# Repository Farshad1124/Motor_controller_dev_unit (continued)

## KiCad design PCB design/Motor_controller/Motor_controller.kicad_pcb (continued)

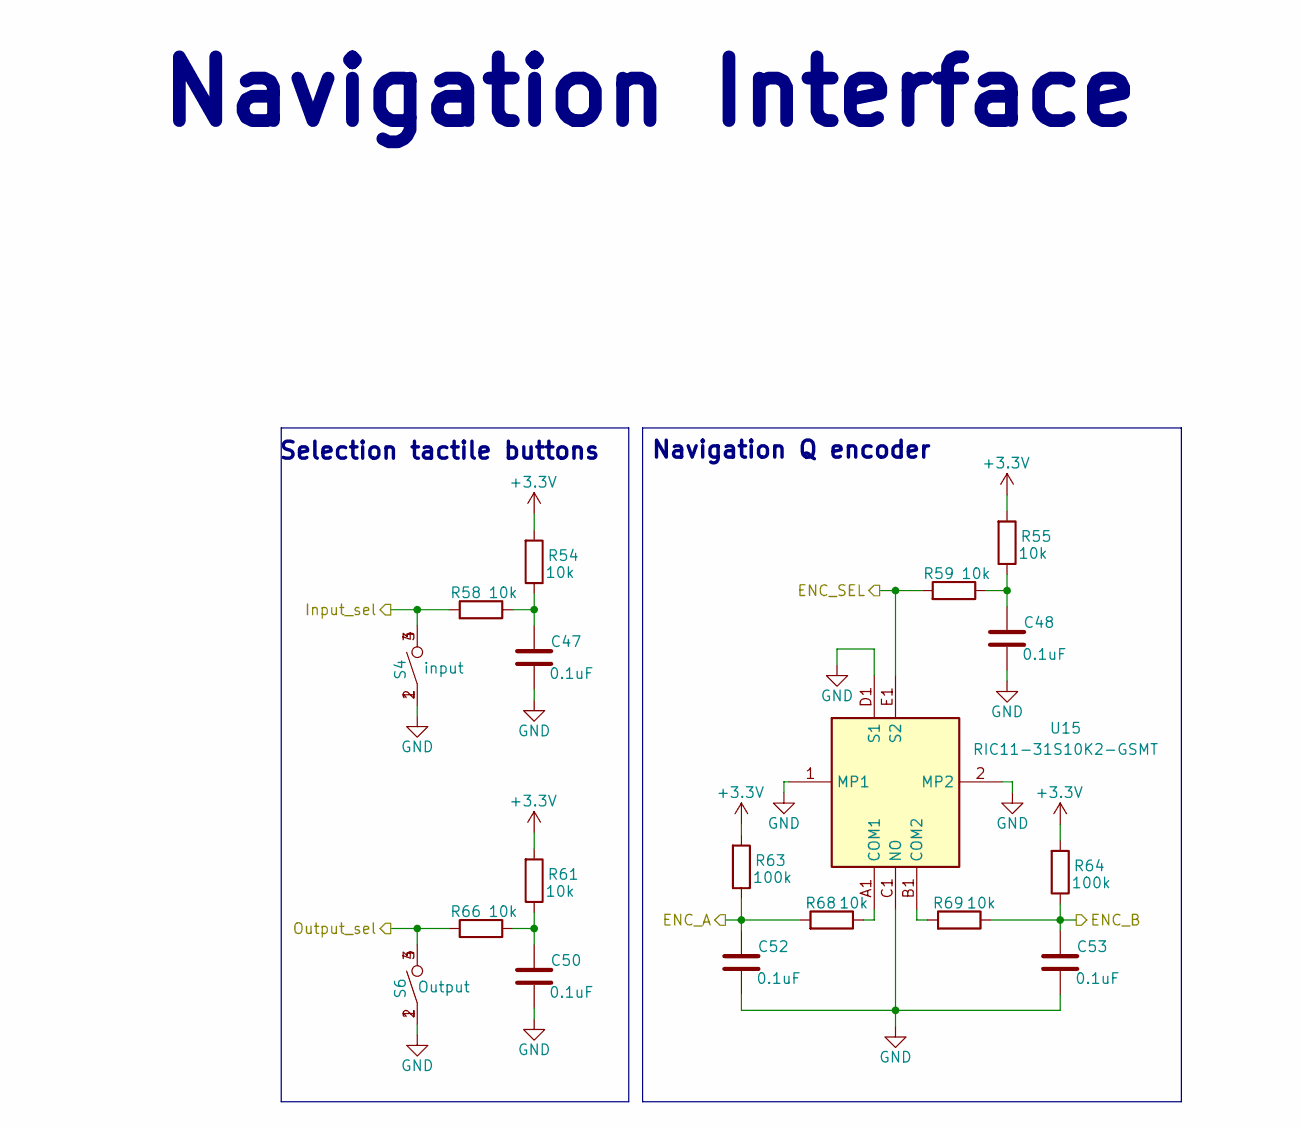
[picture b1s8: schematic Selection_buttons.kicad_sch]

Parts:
C47, C48, C50, C52, C53: 0.1uF; C_0603_1608Metric
R54, R55, R58, R59, R61, R66, R68, R69: 10k; R_0603_1608Metric
R63, R64: 100k; R_0603_1608Metric
S4: input; SMT_FS
S6: Output; SMT_FS
U15: RIC11-31S10K2-GSMT; RIC1131S10K2GSMT; Manufacturer_Part_Number RIC11-31S10K2-GSMT; Mouser Part Number 179-RIC1131S10K2GSMT

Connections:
+3.3V: R54.1, R55.1, R61.1, R63.1, R64.1; also elsewhere on the board
/ENC_A: C52.2, R63.2, R68.1; also elsewhere on the board
/ENC_B: C53.2, R64.2, R69.2; also elsewhere on the board
/ENC_SEL: R59.1, U15.E1 (S2); also elsewhere on the board
/Input_sel: R58.1, S4.3, S4.4; also elsewhere on the board
/Ouput_sel: R66.1, S6.3, S6.4; also elsewhere on the board
GND: C47.1, C48.1, C50.1, C52.1, C53.1, S4.1, S4.2, S6.1, S6.2, U15.1 (MP1), U15.2 (MP2), U15.C1 (NO), U15.D1 (S1); also elsewhere on the board
unnamed: C47.2, R54.2, R58.2
unnamed: C48.2, R55.2, R59.2
unnamed: C50.2, R61.2, R66.2
unnamed: R68.2, U15.A1 (COM1)
unnamed: R69.1, U15.B1 (COM2)

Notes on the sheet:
Navigation Interface
Selection tactile buttons
Navigation Q encoder

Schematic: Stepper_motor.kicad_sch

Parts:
C30, C31, C33: 0.1uF; C_0603_1608Metric
C32: 100uF; CAPAE660X600N; voltage 35v
J8: B4B-XH-A; JST_B4B-XH-A
J9: PHOENIX_1984633
J10: Conn_01x05_Pin; PinHeader_1x05_P2.54mm_Vertical
JP1, JP2, JP3: NPC02SXON-RC; TestPoint_2Pads_Pitch2.54mm_Drill0.8mm
R37: 10k; R_0603_1608Metric
R38, R39, R40: 100; R_0603_1608Metric
R41: 1k; R_0603_1608Metric
TP37, TP38, TP49, TP50, TP51: TestPoint; KEYSTONE_1031; PARTREV B
U11: NC7WZ14P6X; TSOT23-6_419BL_ONS
U12: TMC2208_SILENTSTEPSTICK; MODULE_TMC2208_SILENTSTEPSTICK

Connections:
+3.3V: C30.2, C31.2, C33.2, JP1.2 (B), JP2.2 (B), JP3.2 (B), R37.1, U11.5 (VCC), U12.JP2_7 (VIO); also elsewhere on the board
/SMDIR: R39.1; also elsewhere on the board
/SMEN: J10.5, R37.2, R38.2, U11.1 (A1), U12.JP1_8 (EN); also elsewhere on the board
/SMRX: J10.4, R41.1; also elsewhere on the board
/SMSTEP: R40.1; also elsewhere on the board
/SMTX: J10.3, JP1.1 (A), R41.2, U12.JP1_5 (PDN/UART2); also elsewhere on the board
/Stepper motor/DR: J10.1, R39.2, U12.JP1_1 (DIR)
/Stepper motor/OA1: J8.2, J9.2, TP49.TP, U12.JP2_4 (OA1)
/Stepper motor/OA2: J8.3, J9.3, TP50.TP, U12.JP2_3 (OA2)
/Stepper motor/OB1: J8.1, J9.1, TP38.TP, U12.JP2_5 (OB1)
/Stepper motor/OB2: J8.4, J9.4, TP51.TP, U12.JP2_6 (OB2)
/Stepper motor/STP: J10.2, R40.2, U12.JP1_2 (STEP)
GND: C30.1, C31.1, C32.2, C33.1, TP37.TP, U11.2 (GND), U12.JP2_2 (GND), U12.JP2_8 (GND); also elsewhere on the board
unnamed: JP2.1 (A), U12.JP1_7 (MS1)
unnamed: JP3.1 (A), U12.JP1_6 (MS2)
unnamed: R38.1, U11.6 (Y1)
unnamed: U12.JP1_3 (CLK), U12.JP1_4 (PDN/UART1)
VSM: C32.1, U12.JP2_1 (VM); also elsewhere on the board

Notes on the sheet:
Stepper Motor Driver

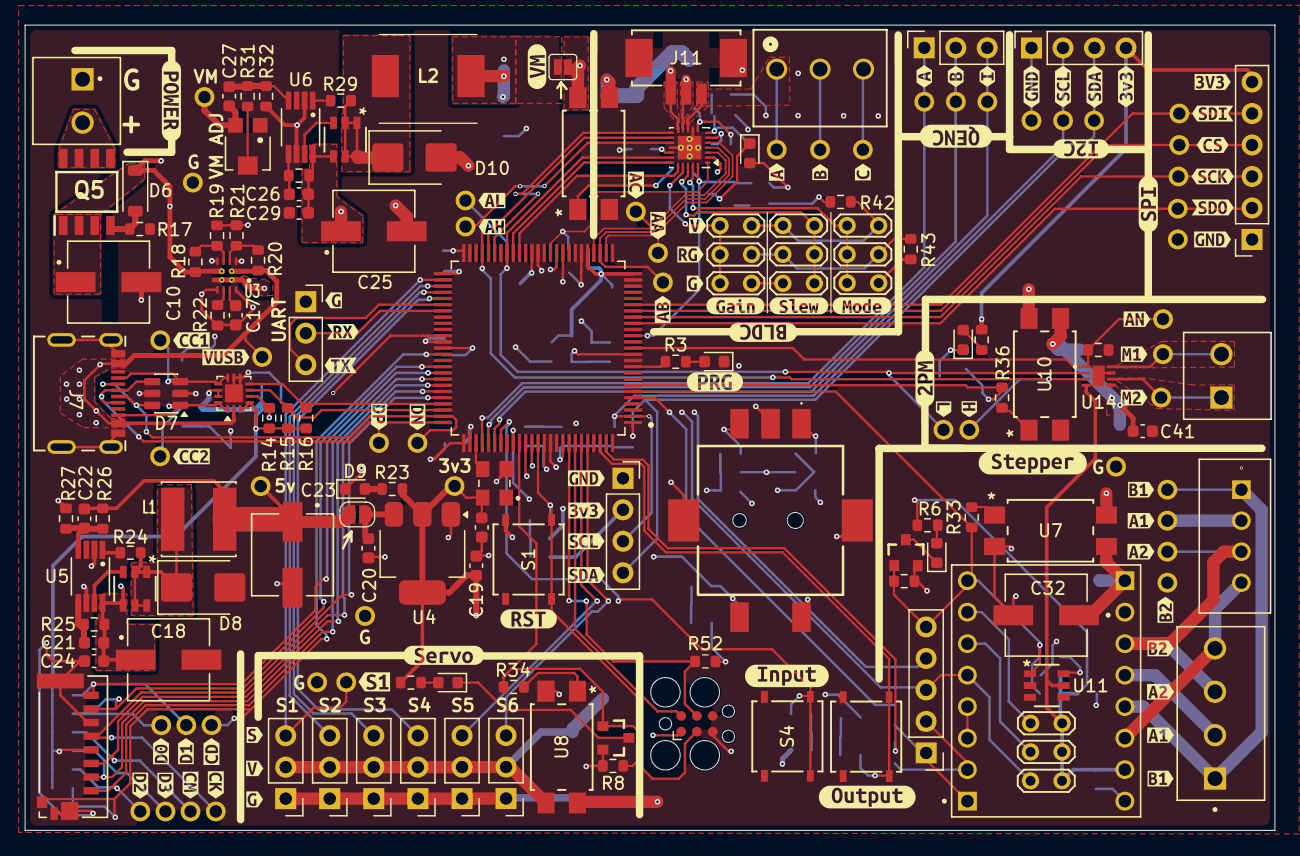
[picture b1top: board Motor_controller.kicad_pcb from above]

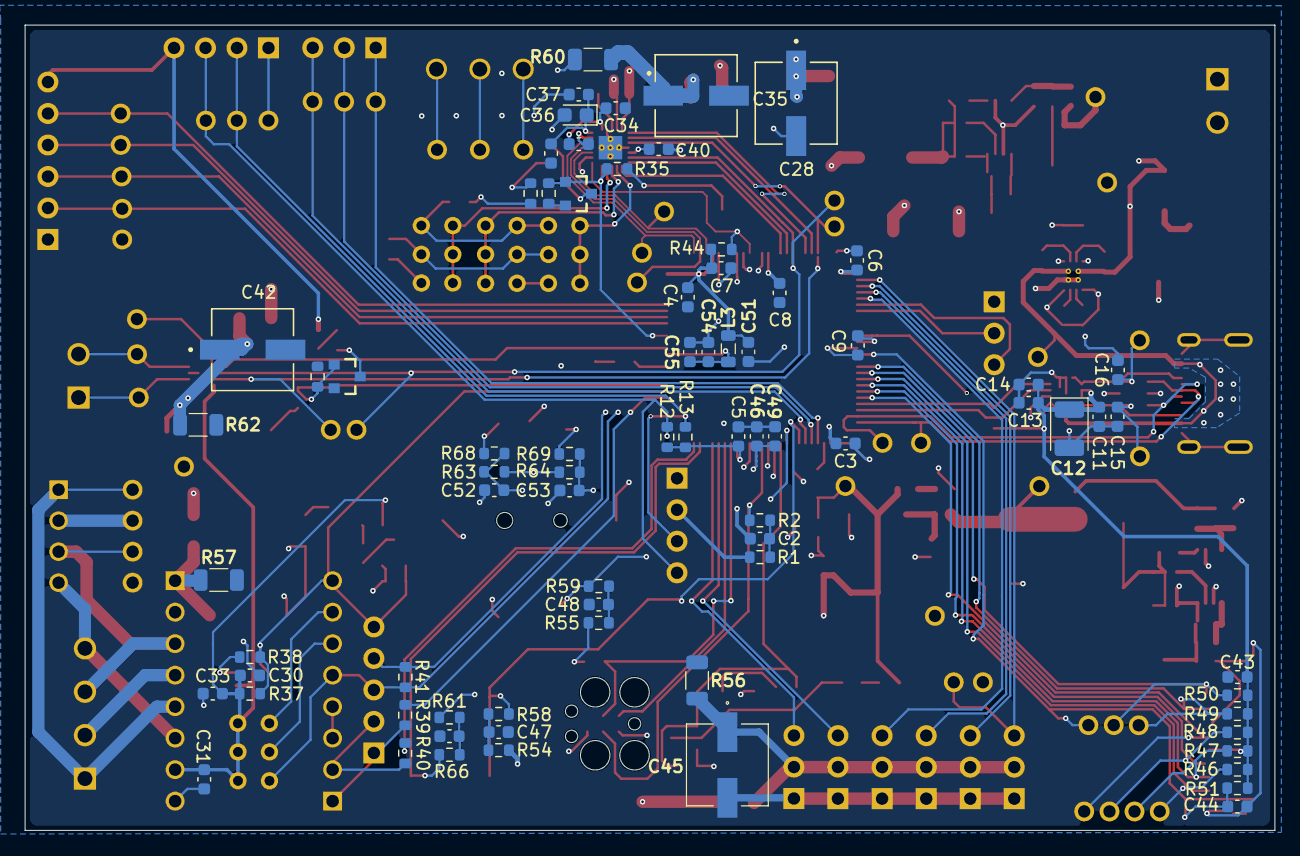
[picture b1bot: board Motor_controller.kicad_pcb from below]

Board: 4 copper layers, 100.8 x 65.0 mm, 319 parts (76 on the bottom side), 134 nets.

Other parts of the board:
kibuzzard-6A6A84AC: G***; kibuzzard-6A6A84AC
kibuzzard-6A6A843B: G***; kibuzzard-6A6A843B
kibuzzard-6A6A844C: G***; kibuzzard-6A6A844C
kibuzzard-6A6A845F: G***; kibuzzard-6A6A845F
kibuzzard-6A6A846C: G***; kibuzzard-6A6A846C
kibuzzard-6A6A8483: G***; kibuzzard-6A6A8483
kibuzzard-6A6A8495: G***; kibuzzard-6A6A8495
kibuzzard-6A6AA16F: G***; kibuzzard-6A6AA16F
kibuzzard-6A6AB0B9: G***; kibuzzard-6A6AB0B9
kibuzzard-6A6AB018: G***; kibuzzard-6A6AB018
kibuzzard-6A6AB028: G***; kibuzzard-6A6AB028
kibuzzard-6A6AB55B: G***; kibuzzard-6A6AB55B
kibuzzard-6A6AB65C: G***; kibuzzard-6A6AB65C
kibuzzard-6A6AB333: G***; kibuzzard-6A6AB333
kibuzzard-6A6AB573: G***; kibuzzard-6A6AB573
kibuzzard-6A6AB741: G***; kibuzzard-6A6AB741
kibuzzard-6A6AB750: G***; kibuzzard-6A6AB750
kibuzzard-6A6D000A: G***; kibuzzard-6A6D000A
kibuzzard-6A6D3F7B: G***; kibuzzard-6A6D3F7B
kibuzzard-6A9B0FE9: G***; kibuzzard-6A9B0FE9
kibuzzard-6A9B0FFC: G***; kibuzzard-6A9B0FFC
kibuzzard-6A67A6FB: G***; kibuzzard-6A67A6FB
kibuzzard-6A67A717: G***; kibuzzard-6A67A717
kibuzzard-6A67B8BD: G***; kibuzzard-6A67B8BD
kibuzzard-6A67B82C: G***; kibuzzard-6A67B82C
kibuzzard-6A67B858: G***; kibuzzard-6A67B858
kibuzzard-6A67D5B7: G***; kibuzzard-6A67D5B7
kibuzzard-6A67D5C9: G***; kibuzzard-6A67D5C9
kibuzzard-6A67D598: G***; kibuzzard-6A67D598
kibuzzard-6A67D603: G***; kibuzzard-6A67D603
kibuzzard-6A67D617: G***; kibuzzard-6A67D617
kibuzzard-6A67D637: G***; kibuzzard-6A67D637
kibuzzard-6A67E5CB: G***; kibuzzard-6A67E5CB
kibuzzard-6A67E545: G***; kibuzzard-6A67E545
kibuzzard-6A67E571: G***; kibuzzard-6A67E571
kibuzzard-6A67F9C7: G***; kibuzzard-6A67F9C7
kibuzzard-6A67F9D9: G***; kibuzzard-6A67F9D9
kibuzzard-6A67F044: G***; kibuzzard-6A67F044
kibuzzard-6A67F87C: G***; kibuzzard-6A67F87C
kibuzzard-6A67F891: G***; kibuzzard-6A67F891
kibuzzard-6A67FEEF: G***; kibuzzard-6A67FEEF
kibuzzard-6A67FFFA: G***; kibuzzard-6A67FFFA
kibuzzard-6A679C3C: G***; kibuzzard-6A679C3C
kibuzzard-6A679C8A: G***; kibuzzard-6A679C8A
kibuzzard-6A679C30: G***; kibuzzard-6A679C30
kibuzzard-6A679C76: G***; kibuzzard-6A679C76
kibuzzard-6A679C91: G***; kibuzzard-6A679C91
kibuzzard-6A679C97: G***; kibuzzard-6A679C97
kibuzzard-6A680EB7: G***; kibuzzard-6A680EB7
kibuzzard-6A680F4D: G***; kibuzzard-6A680F4D
kibuzzard-6A680F98: G***; kibuzzard-6A680F98
kibuzzard-6A680FB2: G***; kibuzzard-6A680FB2
kibuzzard-6A680FF5: G***; kibuzzard-6A680FF5
kibuzzard-6A6800E6: G***; kibuzzard-6A6800E6
kibuzzard-6A6800F9: G***; kibuzzard-6A6800F9
kibuzzard-6A6815D2: G***; kibuzzard-6A6815D2
kibuzzard-6A6822BB: G***; kibuzzard-6A6822BB
kibuzzard-6A6822D3: G***; kibuzzard-6A6822D3
kibuzzard-6A6829BB: G***; kibuzzard-6A6829BB
kibuzzard-6A6977BF: G***; kibuzzard-6A6977BF
kibuzzard-6A69714E, kibuzzard-6A69714E#2: G***; kibuzzard-6A69714E
kibuzzard-6A680004: G***; kibuzzard-6A680004
kibuzzard-6A680011: G***; kibuzzard-6A680011
kibuzzard-6A680102: G***; kibuzzard-6A680102
kibuzzard-6A680116: G***; kibuzzard-6A680116
kibuzzard-6A680514: G***; kibuzzard-6A680514
kibuzzard-6A680958: G***; kibuzzard-6A680958
kibuzzard-6A680974: G***; kibuzzard-6A680974
kibuzzard-6A681364: G***; kibuzzard-6A681364
kibuzzard-6A697161, kibuzzard-6A697161#2: G***; kibuzzard-6A697161
kibuzzard-6A697186, kibuzzard-6A697186#2: G***; kibuzzard-6A697186
kibuzzard-6A697195, kibuzzard-6A697195#2: G***; kibuzzard-6A697195

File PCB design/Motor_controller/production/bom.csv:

Designator,Footprint,Quantity,Value,LCSC Part #
"C1, C11, C14, C2, C24, C29, C3, C30, C31, C33, C34, C37, C4, C41, C43, C44, C47, C48, C49, C5, C50, C52, C53, C55, C6, C7, C8, C9",0603,28,0.1uF,
"C10, C18, C25",CAPAE660X600N,3,22uF,
C12,CP_EIA-3528-12_Kemet-T,1,100uF,
"C13, C17",0603,2,1uF,
"C15, C16",0603,2,330pF,
"C19, C51, C54",0603,3,10uF,
"C20, C38, C39",0603,3,100nF,
"C21, C26",0603,2,1nF,
"C22, C27",0603,2,100pF,
"C23, C28, C32, C45",CAPAE660X600N,4,100uF,
"C35, C42",CAPAE660X600N,2,10uF,
C36,CP_EIA-2012-12_Kemet-R,1,10uF,
"C40, C46",0603,2,4.7uf,
"D1, D2, D3, D4, D5, D9",0603,6,LED,
"D10, D8",D_SMB,2,10BQ040,
D6,D_SOD-123,1,BZT52B12,
D7,SOT-23-6,1,ESDA6V1BC6,
J10,PinHeader_1x05_P2.54mm_Vertical,1,Conn_01x05_Pin,
J11,CONN_532610001-SD_03_MOL,1,532610371,
J12,CONN_1984620_PXC,1,1984620,
"J13, J6",PHOENIX_1984617,2,1984617,
J14,AMPHENOL_10067099-200LF,1,10067099-200LF,
J15,PinHeader_1x03_P2.54mm_Vertical,1,Servo1,
J16,PinHeader_1x03_P2.54mm_Vertical,1,Servo2,
J17,PinHeader_1x03_P2.54mm_Vertical,1,Servo3,
J18,PinHeader_1x03_P2.54mm_Vertical,1,Servo4,
J19,PinHeader_1x03_P2.54mm_Vertical,1,Servo5,
J2,PinSocket_1x06_P2.54mm_Vertical,1,SPI header,
J20,PinHeader_1x03_P2.54mm_Vertical,1,Servo6,
J3,PinSocket_1x04_P2.54mm_Vertical,1,I2C header,
"J4, PDED1",PinSocket_1x03_P2.54mm_Vertical,2,UART header,
J5,PinSocket_1x04_P2.54mm_Vertical,1,OLED header,
J7,USBC_CONN_8p94X6p5X3p16_12L_GCC,1,USB4215-03-A,
J8,JST_B4B-XH-A,1,B4B-XH-A,
J9,PHOENIX_1984633,1,~,
"JP1, JP10, JP11, JP12, JP2, JP3, JP4, JP5, JP6, JP7, JP8, JP9",TestPoint_2Pads_Pitch2.54mm_Drill0.8mm,12,NPC02SXON-RC,
JP13,Jumper_2_NO,1,~,
L1,IND_VLS6045EX-220M,1,22uH,
L2,INDPM7967X540N,1,MPLCV0654L220,
L3,0805,1,10uH,
"MOSFET1, MOSFET2",TSOT23-6_419BL_ONS,2,FDC5614P,
"Q1, Q2, Q3, Q4",SOT23-3,4,SL2302B,
Q5,SOIC127P600X175-8N,1,SI4447ADY-T1-GE3,
"R1, R10, R11, R12, R13, R14, R15, R16, R37, R42, R44, R48, R51, R54, R55, R58, R59, R61, R66, R68, R69, R8, R9",0603,23,10k,
"R17, R18, R20, R46, R47, R49, R50, R63, R64",0603,9,100k,
"R19, R21",0603,2,5k,
"R2, R52",0603,2,330,
"R22, R38, R39, R40",0603,4,100,
"R23, R3, R41",0603,3,1K,
"R24, R29",0603,2,270,
"R25, R30",0603,2,76k,
"R26, R31",0603,2,60k,
"R27, R32",0603,2,20k,
R28,TRIM_TC33X-2-204E,1,200k,
"R33, R34, R35, R36",0603,4,170,
"R4, R5, R6, R7",0603,4,200,
R43,0603,1,47k,
R45,0603,1,1.5k,
S1,SMT_FS,1,Reset,
S4,SMT_FS,1,input,
S6,SMT_FS,1,Output,
"TP1, TP11, TP12, TP13, TP14, TP15, TP16, TP17, TP18, TP19, TP2, TP20, TP21, TP22, TP23, TP24, TP25, TP26, TP27, TP28, TP29, TP30, TP31, TP32, TP33, TP34, TP35, TP36, TP37, TP38, TP39, TP4, TP40, TP41, TP42, TP43, TP44, TP45, TP46, TP47, TP48, TP49, TP50, TP51, TP52, TP6, TP7, TP8",KEYSTONE_1031,48,TestPoint,
U1,QFP50P1600X1600X120-100N,1,ATSAMD51N20A-AUT,
"U10, U7, U8, U9",11-5B201S_TOS,4,TLP3555ATP1_F,
U11,TSOT23-6_419BL_ONS,1,NC7WZ14P6X,
U12,MODULE_TMC2208_SILENTSTEPSTICK,1,TMC2208_SILENTSTEPSTICK,
U13,Texas_RRW0024A_WQFN-24-1EP_3x3mm_P0.4mm_EP1.9x1.9mm_ThermalVias,1,DRV8311H,
U14,WSON8_DSG_TEX,1,DRV8231ADSG,
U15,RIC1131S10K2GSMT,1,RIC11-31S10K2-GSMT,
U2,WQFN-14-1EP_2.5x2.5mm_P0.5mm_EP1.45x1.45mm,1,FUSB302BMPX,
U3,IC_TPS2121RUXR,1,TPS2121RUXR,
U4,SOT-223-3_TabPin2,1,LD1117S33TR_SOT223,
"U5, U6",SOP65P490X110-8N,2,LM3489MMX_NOPB,
Y1,OSC_ECS-2333-160-BN-TR,1,ECS-2333-160-BN-TR,

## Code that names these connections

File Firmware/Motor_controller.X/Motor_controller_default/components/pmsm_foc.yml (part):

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    MCPMSMFOC_ANALOG_FRONT_END_IA_GAIN:
      attributes:
        id: MCPMSMFOC_ANALOG_FRONT_END_IA_GAIN
        label: Gain
      children:
      - children:
        - attributes:
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    MCPMSMFOC_ANALOG_FRONT_END_IB_GAIN:
      attributes:
        id: MCPMSMFOC_ANALOG_FRONT_END_IB_GAIN
        label: Gain
      children:
      - children:
        - attributes:
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            - type: Value
              value: '** Select **'
            - type: Value
              value: PA00
            - type: Value
              value: PA01
            - type: Value
              value: PA02
            - type: Value
              value: PA03
            - type: Value
              value: PA04
            - type: Value
              value: PA05
            - type: Value
              value: PA06
            - type: Value
              value: PA07
            - type: Value
              value: PA08
            - type: Value
              value: PA09
            - type: Value
              value: PA10
            - type: Value
              value: PA11
            - type: Value
              value: PA12
            - type: Value
              value: PA13
            - type: Value
              value: PA14
            - type: Value
              value: PA15
            - type: Value
              value: PA16
            - type: Value
              value: PA17
            - type: Value
              value: PA18
            - type: Value
              value: PA19
            - type: Value
              value: PA20
            - type: Value
              value: PA21
            - type: Value
              value: PA22
            - type: Value
              value: PA23
            - type: Value
              value: PA24
            - type: Value
              value: PA25
            - type: Value
              value: PA27
            - type: Value
              value: PA30
            - type: Value
              value: PA31
            - type: Value
              value: PB00
            - type: Value
              value: PB02
            - type: Value
              value: PB03
            - type: Value
              value: PB04
            - type: Value
              value: PB05
            - type: Value
              value: PB06
            - type: Value
              value: PB07
            - type: Value
              value: PB08
            - type: Value
              value: PB09
            - type: Value
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            - type: Value
              value: PB11
            - type: Value
              value: PB12
            - type: Value
              value: PB13
            - type: Value
              value: PB14
            - type: Value
              value: PB15
            - type: Value
              value: PB16
            - type: Value
              value: PB17
            - type: Value
              value: PB18
            - type: Value
              value: PB19
            - type: Value
              value: PB20
            - type: Value
              value: PB21
            - type: Value
              value: PB22
            - type: Value
              value: PB23
            - type: Value
              value: PB24
            - type: Value
              value: PB25
            - type: Value
              value: PB30
            - type: Value
              value: PB31
            - type: Value
              value: PC00
            - type: Value
              value: PC01
            - type: Value
              value: PC02
            - type: Value
              value: PC03
            - type: Value
              value: PC05
            - type: Value
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            - type: Value
              value: PC10
            - type: Value
              value: PC11
            - type: Value
              value: PC12
            - type: Value
              value: PC13
            - type: Value
              value: PC14
            - type: Value
              value: PC15
            - type: Value
              value: PC16
            - type: Value
              value: PC17
            - type: Value
              value: PC18
            - type: Value
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            - type: Value
              value: PC20
            - type: Value
              value: PC21
            - type: Value
              value: PC24
            - type: Value
              value: PC25
            - type: Value
              value: PC26
            - type: Value
              value: PC27
            - type: Value
              value: PC28
            type: Values
          type: StringList
        type: Attributes
      - children:
        - attributes:
            id: pmsm_foc
            value: PC24
          type: Dynamic
        type: Values
      type: Combo
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      - children:
        - attributes:
            id: pmsm_foc
            value: PC24
          type: Dynamic
        type: Values
      type: String
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            - type: Value
              value: '** Select **'
            - type: Value
              value: PA00
            - type: Value
              value: PA01
            - type: Value
              value: PA02
            - type: Value
              value: PA03
            - type: Value
              value: PA04
            - type: Value
              value: PA05
            - type: Value
              value: PA06
            - type: Value
              value: PA07
            - type: Value
              value: PA08
            - type: Value
              value: PA09
            - type: Value
              value: PA10
            - type: Value
              value: PA11
            - type: Value
              value: PA12
            - type: Value
              value: PA13
            - type: Value
              value: PA14
            - type: Value
              value: PA15
            - type: Value
              value: PA16
            - type: Value
              value: PA17
            - type: Value
              value: PA18
            - type: Value
              value: PA19
            - type: Value
              value: PA20
            - type: Value
              value: PA21
            - type: Value
              value: PA22
            - type: Value
              value: PA23
            - type: Value
              value: PA24
            - type: Value
              value: PA25
            - type: Value
              value: PA27
            - type: Value
              value: PA30
            - type: Value
              value: PA31
            - type: Value
              value: PB00
            - type: Value
              value: PB01
            - type: Value
              value: PB02
            - type: Value
              value: PB03
            - type: Value
              value: PB04
            - type: Value
              value: PB05
            - type: Value
              value: PB06
            - type: Value
              value: PB07
            - type: Value
              value: PB08
            - type: Value
              value: PB09
            - type: Value
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            - type: Value
              value: PB11
            - type: Value
              value: PB12
            - type: Value
              value: PB13
            - type: Value
              value: PB14
            - type: Value
              value: PB15
            - type: Value
              value: PB16
            - type: Value
              value: PB17
            - type: Value
              value: PB18
            - type: Value
              value: PB19
            - type: Value
              value: PB20
            - type: Value
              value: PB21
            - type: Value
              value: PB22
            - type: Value
              value: PB23
            - type: Value
              value: PB24
            - type: Value
              value: PB25
            - type: Value
              value: PB30
            - type: Value
              value: PB31
            - type: Value
              value: PC00
            - type: Value
              value: PC01
            - type: Value
              value: PC02
            - type: Value
              value: PC03
            - type: Value
              value: PC05
            - type: Value
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            - type: Value
              value: PC10
            - type: Value
              value: PC11
            - type: Value
              value: PC12
            - type: Value
              value: PC13
            - type: Value
              value: PC14
            - type: Value
              value: PC15
            - type: Value
              value: PC16
            - type: Value
              value: PC17
            - type: Value
              value: PC18
            - type: Value
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            - type: Value
              value: PC20
            - type: Value
              value: PC21
            - type: Value
              value: PC25
            - type: Value
              value: PC26
            - type: Value
              value: PC27
            - type: Value
              value: PC28
            type: Values
          type: StringList
        type: Attributes
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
